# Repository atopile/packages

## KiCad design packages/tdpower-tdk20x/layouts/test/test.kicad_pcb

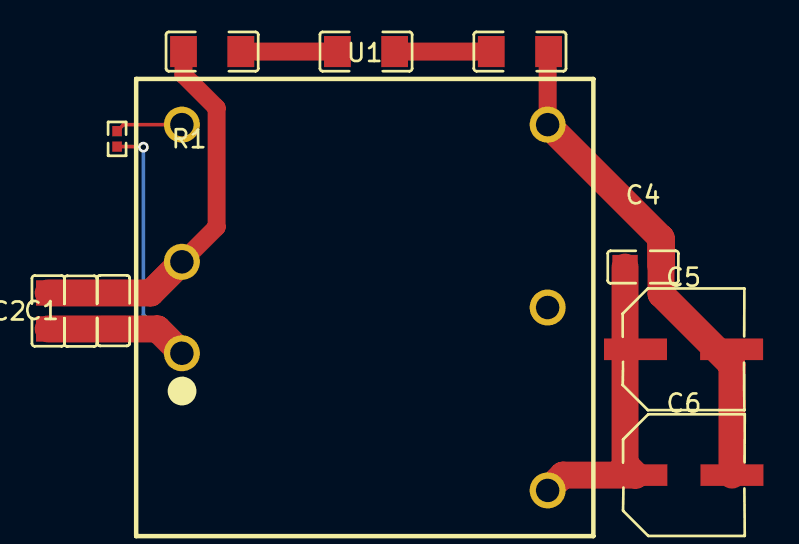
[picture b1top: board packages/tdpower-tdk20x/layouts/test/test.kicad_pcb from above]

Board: 2 copper layers, 11 parts (0 on the bottom side), 7 nets.

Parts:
C1, C2, C3: 10µF ±10% 50V X5R; C0805
C4: 1µF ±10% 50V X7R; C0805
C5, C6: 100µF ±20%; CAP-SMD_BD6.3-L6.6-W6.6-FD
C7, C8, C9: 2.2nF ±10% 1kV X7R; C1206
R1: 10kΩ ±1% 62.5mW; R0402
U1: PWRM-TH_TDPOWER_TDK20-XXSXXWH

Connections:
CNT: R1.1, U1.3
VOpos: C4.1, C5.1, C6.1, U1.6
converter-net: C7.2, C8.1
converter-net-1: C8.2, C9.1
gnd: C1.2, C2.2, C3.2, C7.1, U1.2
gnd-1: C4.2, C5.2, C6.2, C9.2, U1.4
hv: C1.1, C2.1, C3.1, R1.2, U1.1

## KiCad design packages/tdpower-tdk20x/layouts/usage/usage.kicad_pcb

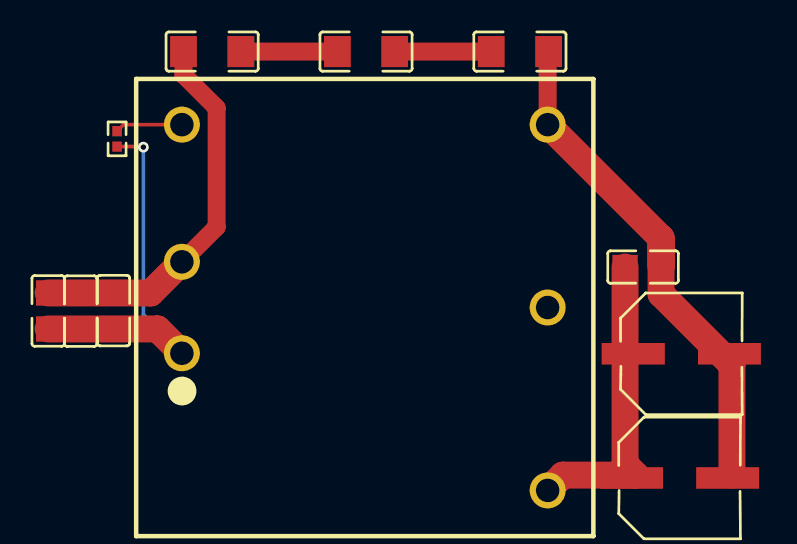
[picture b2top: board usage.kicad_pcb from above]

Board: 2 copper layers, 11 parts (0 on the bottom side), 7 nets.

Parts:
C1, C2, C3, C4: [capacitance: unknown]; C0805
C5, C6, C7: [capacitance: unknown]; C1206
C8, C9: CAP-SMD_BD6.3-L6.6-W6.6-FD
R1: [resistance: unknown]; R0402
U1: PWRM-TH_TDPOWER_TDK20-XXSXXWH

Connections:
CNT: R1.1, U1.3
hv: C1.1, C2.1, C3.1, R1.2, U1.1
lv: C4.2, C7.2, C8.2, C9.2, U1.4
output_cap_1-power-hv: C4.1, C8.1, C9.1, U1.6
y_caps[0]-power-hv: C1.2, C2.2, C3.2, C5.1, U1.2
y_caps[1]-power-hv: C5.2, C6.1
y_caps[2]-power-hv: C6.2, C7.1

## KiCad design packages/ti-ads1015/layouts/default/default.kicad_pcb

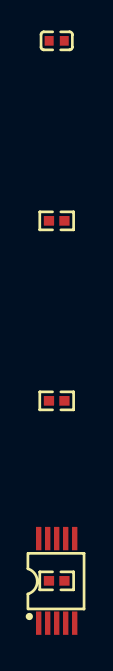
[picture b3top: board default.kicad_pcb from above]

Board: 2 copper layers, 5 parts (0 on the bottom side), 6 nets, no tracks yet.

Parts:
C1: 100nF; C0402
R1, R2, R3: 10kΩ; R0402
U1: VSSOP-10_L3.0-W3.0-P0.50-LS4.9-BL

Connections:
ALERT_RDY: R1.1, U1.2
SCL: R2.1, U1.10
SDA: R3.1, U1.9
hv: C1.1, U1.8
i2c-hv: R2.2, R3.2
lv: C1.2, U1.1, U1.3

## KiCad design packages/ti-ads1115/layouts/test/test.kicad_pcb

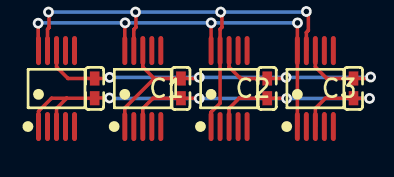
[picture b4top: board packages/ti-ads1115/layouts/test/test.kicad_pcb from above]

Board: 2 copper layers, 8 parts (0 on the bottom side), 4 nets.

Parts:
C1, C2, C3, C4: 100nF ±10% 16V X7R; C0402
U1, U2, U3, U4: MSOP-10_L3.0-W3.0-P0.50-LS5.0-BL

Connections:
SCL: U1.10, U2.10, U3.10, U4.1, U4.10
SDA: U1.9, U2.9, U3.1, U3.9, U4.9
gnd: C1.2, C2.2, C3.2, C4.2, U1.1, U1.3, U2.3, U3.3, U4.3
hv: C1.1, C2.1, C3.1, C4.1, U1.8, U2.1, U2.8, U3.8, U4.8
